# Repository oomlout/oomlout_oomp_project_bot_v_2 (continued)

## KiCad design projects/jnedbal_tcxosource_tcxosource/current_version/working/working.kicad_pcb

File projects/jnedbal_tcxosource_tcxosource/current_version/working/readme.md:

# tcxosource
 
## summary 
* id: jnedbal_tcxosource_tcxosource
* user: jnedbal
* name: tcxosource
* board: tcxosource
* repo: https://github.com/jnedbal/TCXOsource
* src_file_repo_kicad_pcb: TCXOsource.kicad_pcb
* src_file_repo_kicad_pcb_link: https://github.com/jnedbal/TCXOsource/tree/master/TCXOsource.kicad_pcb

* src_file_repo_sch: 
* src_file_repo_sch_link: https://github.com/jnedbal/TCXOsource/tree/master/
* full details link: https://github.com/oomlout/oomlout_oomp_project_bot_v_2/tree/main/projects/jnedbal_tcxosource_tcxosource/current_version/working

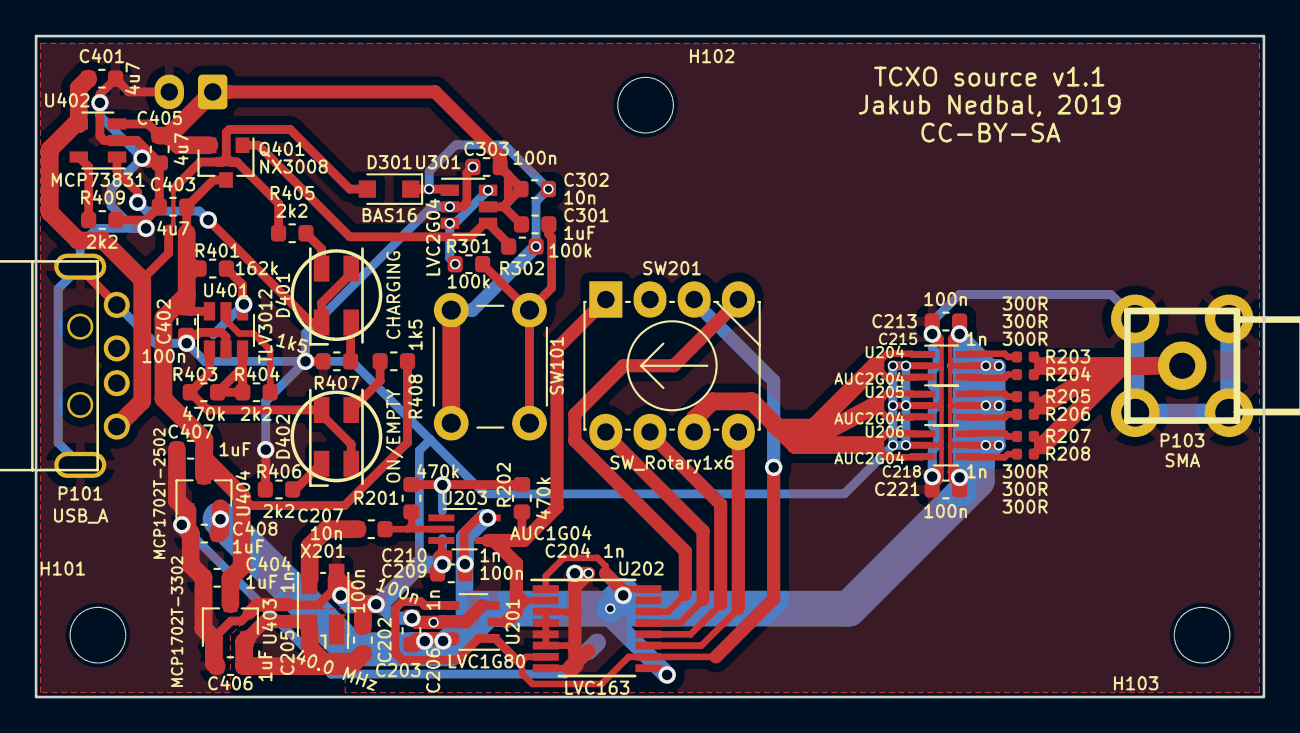
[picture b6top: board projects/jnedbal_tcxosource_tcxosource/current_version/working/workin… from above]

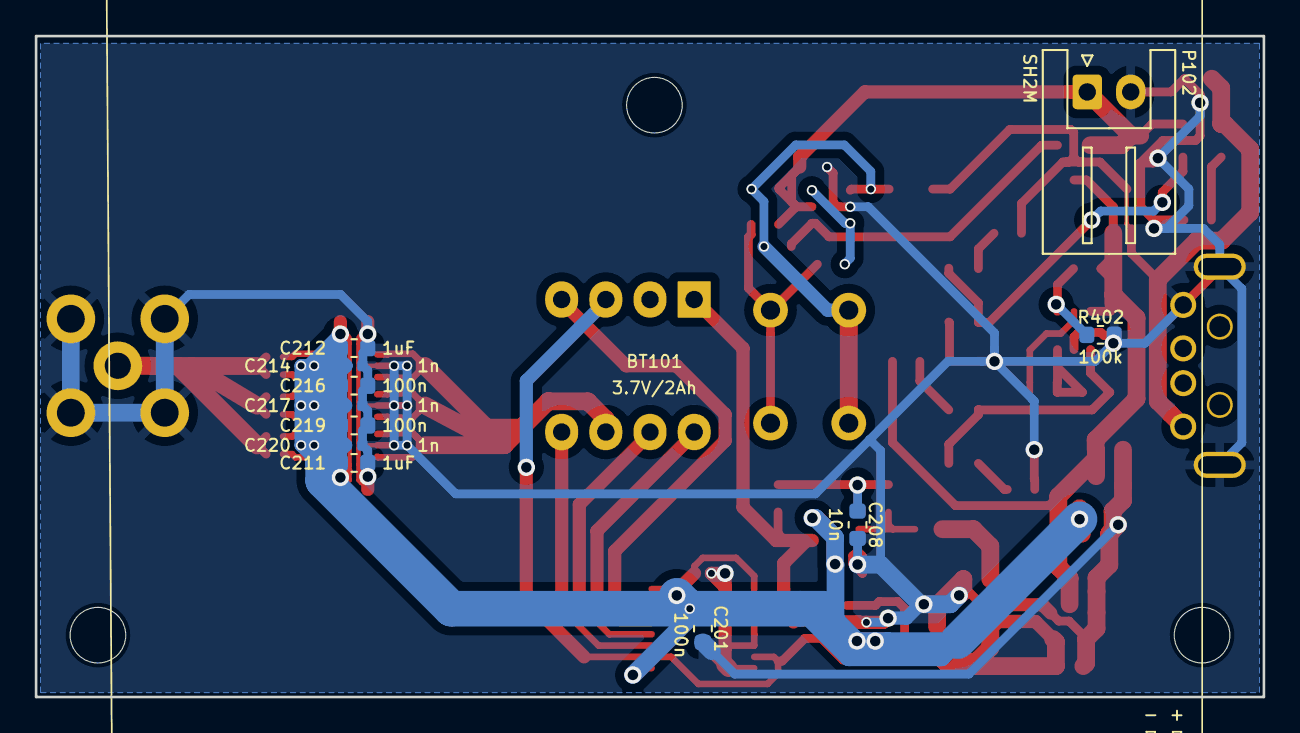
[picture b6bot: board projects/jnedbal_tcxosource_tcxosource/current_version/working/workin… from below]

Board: 2 copper layers, 70.6 x 38.0 mm, 76 parts (12 on the bottom side), 37 nets.

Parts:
BT101: 3.7V/2Ah; MIKROE-1120
C201, C202, C203, C209, C213, C216, C218, C219, C303, C402: 100n; C_0603_1608Metric
C204, C205, C206, C210, C214, C215, C217, C220, C221: 1n; C_0402_1005Metric
C207, C208, C302: 10n; C_0603_1608Metric
C211, C212, C301, C404, C406, C407, C408: 1uF; C_0603_1608Metric
C401, C403, C405: 4u7; C_0603_1608Metric
D301: BAS16; D_SOD-323_HandSoldering
D401, D402: LED_R/G; LEDdual_3.2x2.8
H101, H102, H103: MountingHole; MountingHole_3.2mm_M3
P101: USB_A; Molex_USB_A
P102: SH2M; JST_XH_S2B-XH-A_1x02_P2.50mm_Horizontal
P103: SMA
Q401: NX3008; SOT-23
R201, R202, R403: 470k; R_0603_1608Metric
R203, R204, R205, R206, R207, R208: 300R; R_0402_1005Metric
R301, R302, R402: 100k; R_0603_1608Metric
R401: 162k; R_0603_1608Metric
R404, R405, R406, R409: 2k2; R_0603_1608Metric
R407, R408: 1k5; R_0603_1608Metric
SW101: SW_Push; SW_PUSH_6mm_H13mm
SW201: SW_Rotary1x6; Nidec_Copal_SS-10-16
U201: LVC1G80; TSOP-5_1.65x3.05mm_P0.95mm
U202: LVC163; TSSOP-16_4.4x5mm_P0.65mm
U203: AUC1G04; SOT-353_SC-70-5_Handsoldering
U204, U205, U206: AUC2G04; SOT-363_SC-70-6_Handsoldering
U301: LVC2G04; SOT-23-6
U401: TLV3012; SOT-23-6
U402: MCP73831; SOT-23-5
U403: MCP1702T-3302; SOT-23
U404: MCP1702T-2502; SOT-23
X201: 40.0 MHz; Oscillator_SMD_EuroQuartz_XO32-4Pin_3.2x2.5mm_HandSoldering

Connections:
+2V5: C201.2, C203.2, C204.2, C206.2, C209.2, C210.1, C211.1, C212.1, C213.2, C214.1, C215.1, C216.2, C217.1, C218.2, C219.2, C220.1, C221.1, C408.1, U201.5, U202.1, U202.9, U202.16, U203.5, U204.5, U205.5, U206.5, U404.2
+3V3: C202.2, C205.2, C406.1, U403.2, X201.4
+3V8: C402.2, C403.1, C404.1, C407.1, Q401.3, R401.1, R408.1, U401.6, U403.3, U404.3
+5V: C401.1, D301.2, P101.1, R405.1, U402.4
+BATT: C301.1, C302.1, C303.2, C405.1, P102.1, Q401.2, U301.5, U402.3
/Charger & Power Supply/Bgrn: D402.2, R408.2
/Charger & Power Supply/Bred: D402.3, R406.1
/Charger & Power Supply/Cgrn: D401.4, R407.1
/Charger & Power Supply/Cred: D401.1, R405.2
/Charger & Power Supply/PROG: R409.1, U402.5
/Charger & Power Supply/REF: R404.2, U401.5
/Charger & Power Supply/STAT: D401.2, D401.3, U402.1
/Charger & Power Supply/TH: R403.1, R404.1, U401.3
/Charger & Power Supply/VSENSE: R401.2, R402.1, U401.4
/Charger & Power Supply/~V_OK: D402.1, D402.4, R403.2, U401.1
/SWITCH1: C301.2, R301.2, SW101.2
/SWITCH2: C302.2, D301.1, R302.2, SW101.1, U301.1
/TCXO/OUT: P103.1, R203.1, R204.1, R205.1, R206.1, R207.1, R208.1
/switch/POWER_ON: Q401.1, R302.1, U301.4
GND: C201.1, C202.1, C203.1, C204.1, C205.1, C206.1, C208.2, C209.1, C210.2, C211.2, C212.2, C213.1, C214.2, C215.2, C216.1, C217.2, C218.1, C219.1, C220.2, C221.2, C303.1, C401.2, C402.1, C403.2, C404.2, C405.2, C406.2, C407.2, C408.2, P101.4, P101.5, P102.2, P103.2, P103.3, P103.4, P103.5, R402.2, R406.2, R407.2, R409.2, U201.3, U202.3, U202.4, U202.5, U202.6, U202.8, U203.3, U204.2, U205.2, U206.2, U301.2, U401.2, U402.2, U403.1, U404.1, X201.2
unnamed: C207.1, R201.2, U203.2
unnamed: C207.2, X201.3
unnamed: C208.1, R201.1, R202.2
unnamed: R202.1, SW201.1, U201.2, U202.2, U203.4
unnamed: R203.2, U204.6
unnamed: R204.2, U204.4
unnamed: R205.2, U205.6
unnamed: R206.2, U205.4
unnamed: R207.2, U206.6
unnamed: R208.2, U206.4
unnamed: R301.1, U301.3, U301.6
unnamed: SW201.3, U201.1, U201.4, U202.7, U202.10
unnamed: SW201.4, U202.14
unnamed: SW201.5, U202.13
unnamed: SW201.6, U202.12
unnamed: SW201.7, U204.1, U204.3, U205.1, U205.3, U206.1, U206.3
unnamed: SW201.8, U202.11

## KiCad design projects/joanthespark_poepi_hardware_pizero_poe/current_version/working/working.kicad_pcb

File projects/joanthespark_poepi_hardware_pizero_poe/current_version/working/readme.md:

# poepi_hardware
 
## summary 
* id: joanthespark_poepi_hardware_pizero_poe
* user: joanthespark
* name: poepi_hardware
* board: pizero_poe
* repo: https://github.com/JoanTheSpark/PoEPi-hardware
* src_file_repo_kicad_pcb: ws2812-controller/pizero-poe.kicad_pcb
* src_file_repo_kicad_pcb_link: https://github.com/JoanTheSpark/PoEPi-hardware/tree/master/ws2812-controller/pizero-poe.kicad_pcb

* src_file_repo_sch: 
* src_file_repo_sch_link: https://github.com/JoanTheSpark/PoEPi-hardware/tree/master/
* full details link: https://github.com/oomlout/oomlout_oomp_project_bot_v_2/tree/main/projects/joanthespark_poepi_hardware_pizero_poe/current_version/working

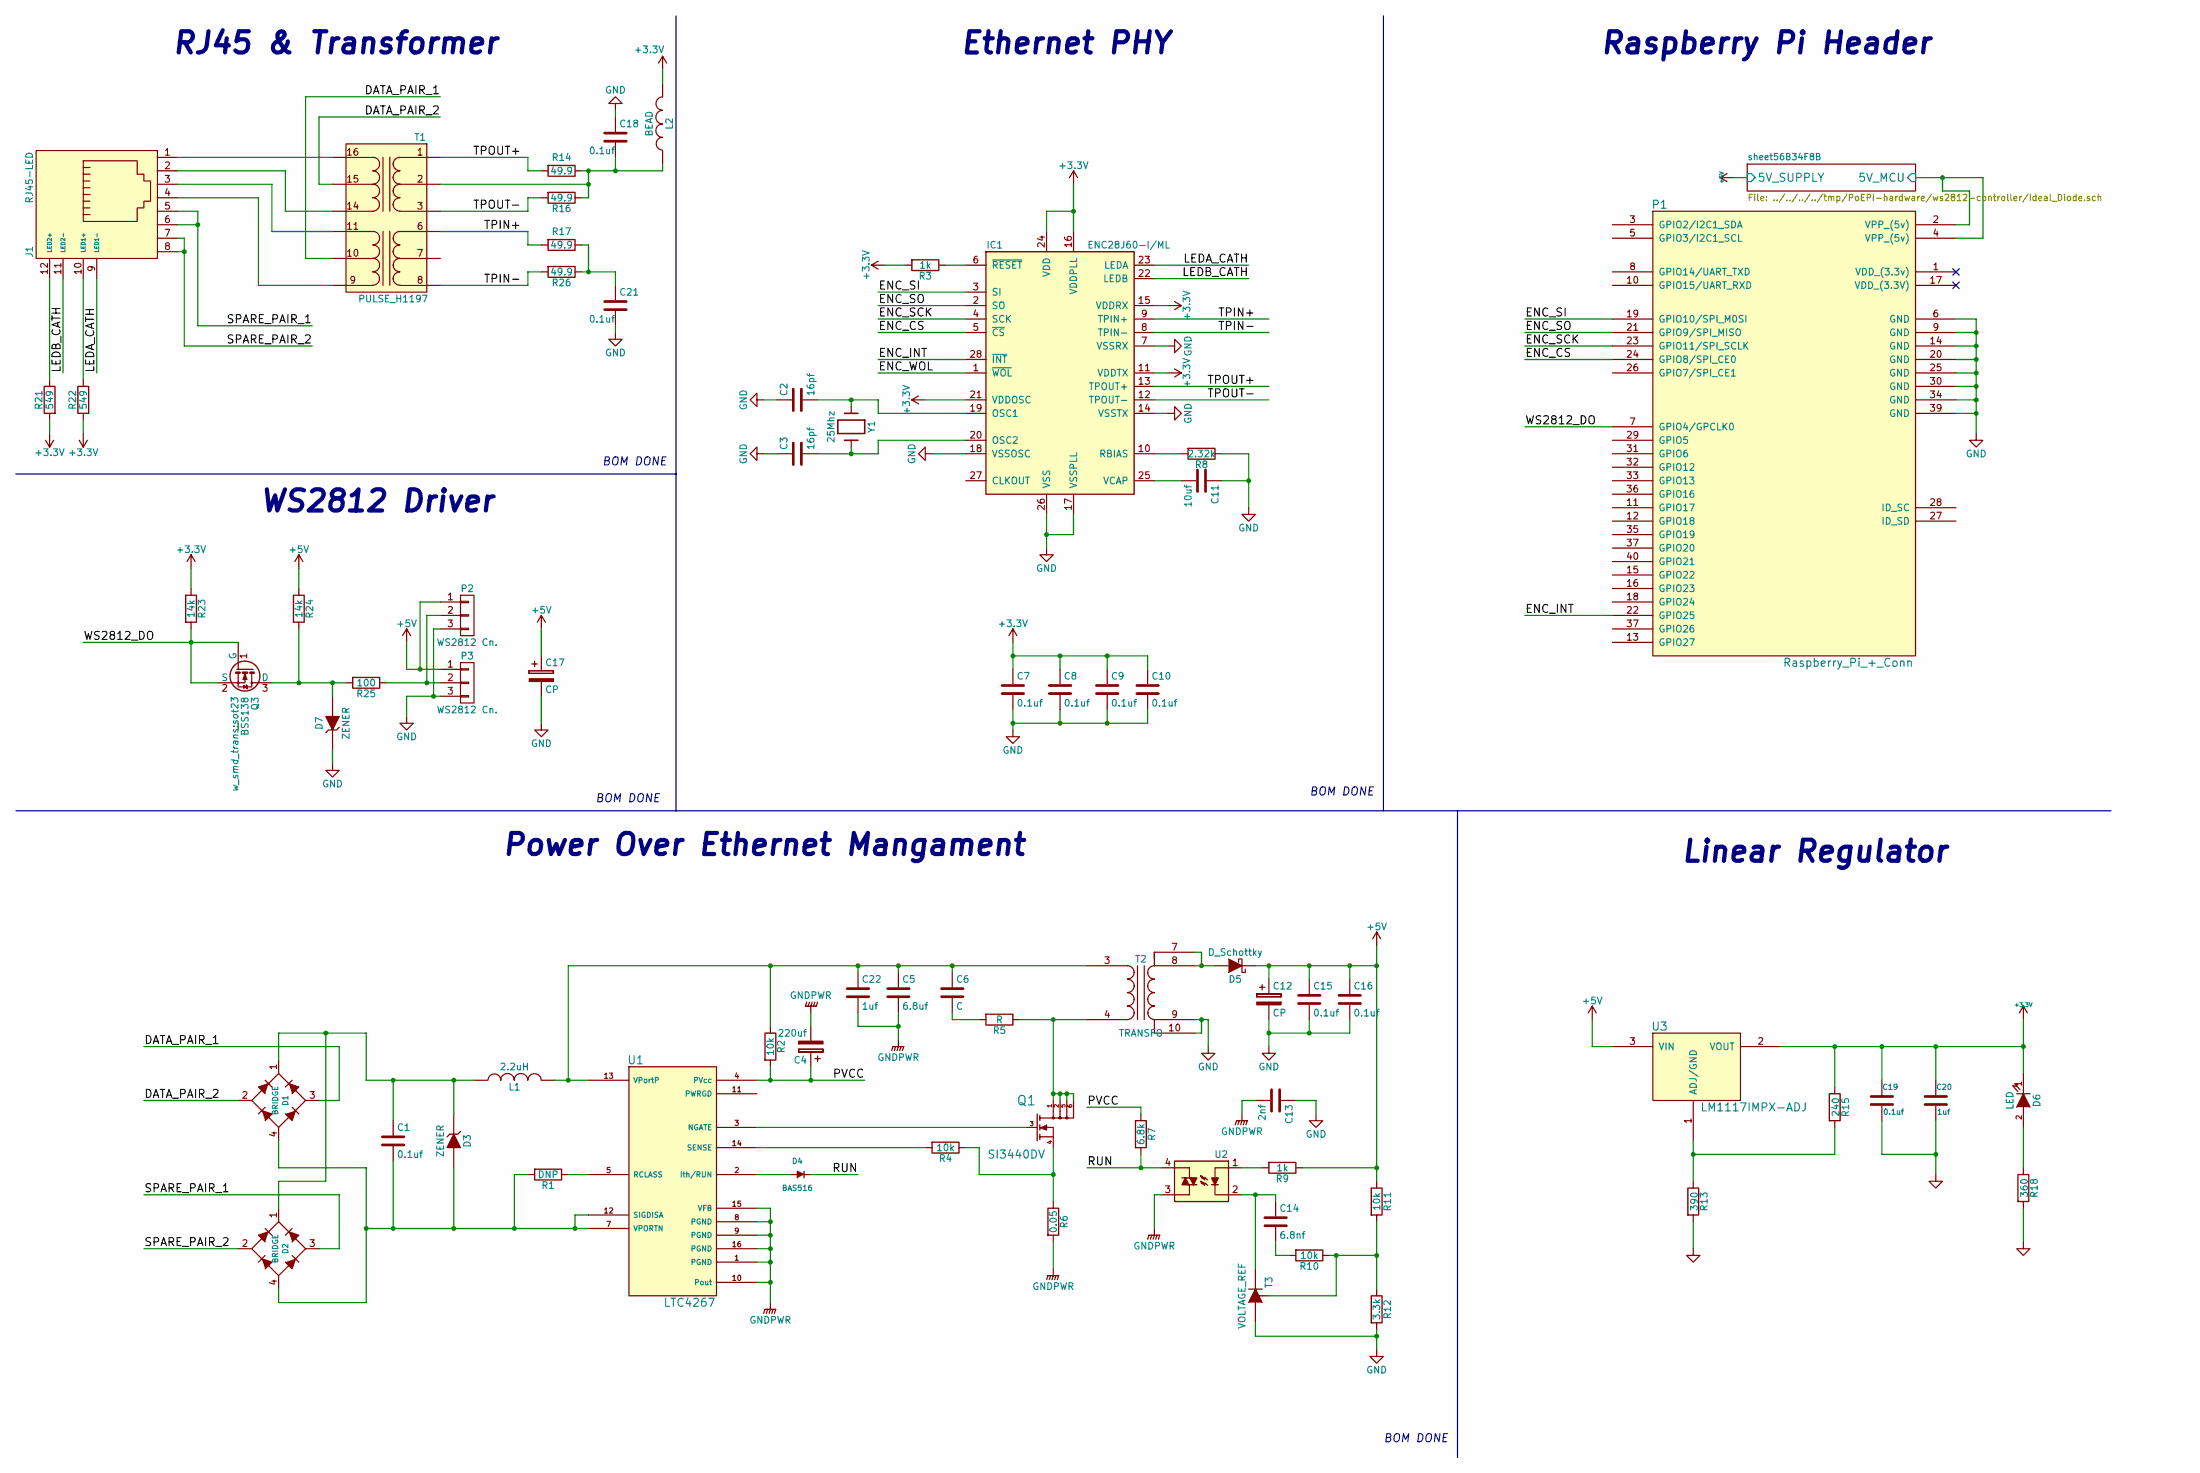
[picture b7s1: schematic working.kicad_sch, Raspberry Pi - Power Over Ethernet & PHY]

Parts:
C1, C7, C8, C9, C18, C19, C21: 0.1uf; c_0402; Mouser Part No. 710-885012105001
C2, C3: 16pf; c_0402; Mouser Part No. 81-GRM1555C1H160JA1D
C4: 220uf; c_tant_B; Mouser Part No. 581-TAJB475K025R
C5: 6.8uf; c_tant_D; Mouser Part No. 74-293D685X9050D2TE3
C6: C; c_0402
C10, C15, C16: 0.1uf; c_0603; Mouser Part No. 710-885012105001
C11: 10uf; c_0603; Mouser Part No. 81-ZRB18AR61C106ME1L
C12: CP; c_elec_4x4.5; Mouser Part No. 667-EEE-1AA330WR
C13: 2nf; c_0603; Mouser Part No. 81-GRM1885C1H202JA1D
C14: 6.8nf; c_0402; Mouser Part No. 81-GRM155R71H682KA8D
C17: CP; c_elec_8x6.5; Mouser Part No. 667-EEE-1AA221P
C20: 1uf; c_0402; Mouser Part No. 810-C1005X5R1H104K
C22: 1uf; c_0805; Mouser Part No. 810-C2012X7S2A105K
D1, D2: BRIDGE; MBS; Mouser Part No. 621-HD01-T
D3: ZENER; do214ac; Mouser Part No. 576-SMAJ58A
D4: BAS516; sod523; Mouser Part No. 771-BAS516-T/R
D5: D_Schottky; do214ab; Mouser Part No. 621-B360A-F
D6: LED; Led_0603; Mouser Part No. 743-HT-191USD
D7: ZENER; sod123; Mouser Part No. 771-BZT52HB5V1115
IC1: ENC28J60-I/ML; qfn-28; Mouser Part No. 579-ENC28J60-I/ML
J1: RJ45-LED; rj45-tyco-2-406549-7; Mouser Part No. 710-615008137421
L1: 2.2uH; inductor_smd_1008; Mouser Part No. 81-LQM2HPN2R2MEHL
L2: BEAD; inductor_smd_0402; Mouser Part No. 81-BLM15AG102SN1D
P1: Raspberry_Pi_+_Conn
P2: WS2812 Cn.; pin_strip_3
P3: WS2812 Cn.; pin_strip_3-90
Q1: SI3440DV; tsot-6; Mouser Part No. 781-SI3440DV-E3
Q3: BSS138; sot23; Mouser Part No. 512-BSS138
R1: DNP; r_0402
R2, R4, R10, R11: 10k; r_0402; Mouser Part No. 754-RR0510P-103D
R3: 1k; r_0402; Mouser Part No. 754-RR0510P-102D
R5: R; r_0402
R6: 0.05; r_1206; Mouser Part No. 660-UR732BTTD50L0F
R7: 6.8k; r_0402; Mouser Part No. 754-RR0510P-682D
R8: 2.32k; r_0402; Mouser Part No. 667-ERJ-2RKF2321X
R9: 1k; r_0402
R12: 3.3k; r_0402; Mouser Part No. 754-RR0510P-332D
R13: 390; r_0402; Mouser Part No. 594-MCT06030C3900FP5
R14, R16, R17, R26: 49.9; r_0402; Mouser Part No. 660-RK73H1ETQTP49R9F
R15: 240; r_0402; Mouser Part No. 754-RR0816P-241D
R18: 360; r_0402; Mouser Part No. 71-CRCW0603316RFKEB
R21, R22: 549; r_0402; Mouser Part No. 667-ERJ-2RKF5490X
R23, R24: 14k; r_0402; Mouser Part No. 667-ERJ-2RKF1402X
R25: 100; r_0402; Mouser Part No. 71-CRCW0402-100-E3
T1: PULSE_H1197; H2019; Mouser Part No. 673-H1197FNL
T2: TRANSFO; PoE_TRANS; Mouser Part No. 710-7491199501
T3: VOLTAGE_REF; sot23; Mouser Part No. 863-TLV431BSN1T1G
U1: LTC4267; ssop-16; Digikey Part No. LTC4267CGN-3#PBF-ND
U2: PAS291; OPTO_ISO; Mouser Part No. 551-PS2911-1-K-AX
U3: LM1117IMPX-ADJ; sot223; Mouser Part No. 926-M1117IMPXADJNOPB
Y1: 25Mhz; crystal_smd_5x3.2mm; Mouser Part No. 774-445I23D25M00000

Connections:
+3V3: C7.1, C8.1, C9.1, C10.1, C19.1, C20.1, D6.1 (K), IC1.11 (VDDTX), IC1.15 (VDDRX), IC1.16 (VDDPLL), IC1.21 (VDDOSC), IC1.24 (VDD), L2.2, R3.2, R15.1, R21.2, R22.2, R23.1, U3.2 (VOUT)
+5V: C12.1, C15.1, C16.1, C17.1, D5.1 (K), P2.1, P3.1, R9.1, R11.1, R24.1, U3.3 (VIN); also elsewhere on the board
/DATA_PAIR_1: D1.3 (~2), T1.10
/DATA_PAIR_2: D1.2 (~1), T1.15
/ENC_CS: IC1.5 (~CS), P1.24 (GPIO8/SPI_CE0)
/ENC_INT: IC1.28 (~INT), P1.22 (GPIO25)
/ENC_SCK: IC1.4 (SCK), P1.23 (GPIO11/SPI_SCLK)
/ENC_SI: IC1.3 (SI), P1.19 (GPIO10/SPI_M0SI)
/ENC_SO: IC1.2 (SO), P1.21 (GPIO9/SPI_MISO)
/ENC_WOL: IC1.1 (~WOL)
/LEDA_CATH: IC1.23 (LEDA), J1.9 (LED1-)
/LEDB_CATH: IC1.22 (LEDB), J1.11 (LED2-)
/PVCC: C4.1, R2.2, R7.1, U1.4 (PVcc)
/RUN: D4.2 (K), R7.2, U2.4
/SPARE_PAIR_1: D2.3 (~2), J1.5, J1.6
/SPARE_PAIR_2: D2.2 (~1), J1.7, J1.8
/TPIN+: IC1.9 (TPIN+), R17.2, T1.6 (PR1)
/TPIN-: IC1.8 (TPIN-), R26.2, T1.8 (PR2)
/TPOUT+: IC1.13 (TPOUT+), R14.2, T1.1 (PR1)
/TPOUT-: IC1.12 (TPOUT-), R16.2, T1.3 (PR2)
/WS2812_DO: P1.7 (GPIO4/GPCLK0), Q3.1 (G), Q3.2 (S), R23.2
/sheet56B34F8B/5V_MCU: P1.2 (VPP_(5v)), P1.4 (VPP_(5v)); also elsewhere on the board
GND: C2.1, C3.1, C7.2, C8.2, C9.2, C10.2, C11.1, C12.2, C13.1, C15.2, C16.2, C17.2, C18.1, C19.2, C20.2, C21.2, D7.1 (K), IC1.7 (VSSRX), IC1.14 (VSSTX), IC1.17 (VSSPLL), IC1.18 (VSSOSC), IC1.26 (VSS), P1.6 (GND), P1.9 (GND), P1.14 (GND), P1.20 (GND), P1.25 (GND), P1.30 (GND), P1.34 (GND), P1.39 (GND), P2.3, P3.3, R8.1, R12.2, R13.2, R18.2, T2.9 (SA), T2.10, T3.2 (A); also elsewhere on the board
GNDPWR: C4.2, C5.2, C13.2, C22.2, R6.2, U1.1 (PGND), U1.8 (PGND), U1.9 (PGND), U1.10 (Pout), U1.15 (VFB), U1.16 (PGND), U2.3
unnamed: C1.1, D1.1 (V+), D2.1 (V+), D3.1 (K), L1.1
unnamed: C1.2, D1.4 (V-), D2.4 (V-), D3.2 (A), R1.2, U1.7 (VPORTN), U1.12 (SIGDISA)
unnamed: C2.2, IC1.19 (OSC1), Y1.1
unnamed: C3.2, IC1.20 (OSC2), Y1.2
unnamed: C6.2, R5.2
unnamed: C11.2, IC1.25 (VCAP)
unnamed: C14.1, T3.3 (K), U2.2
unnamed: C14.2, R10.2
unnamed: C18.2, L2.1, R14.1, R16.1, T1.2 (PM)
unnamed: C21.1, R17.1, R26.1
unnamed: C5.1, C6.1, C22.1, L1.2, R2.1, T2.3 (AA), U1.13 (VPortP)
unnamed: D4.1 (A), U1.2 (Ith/RUN)
unnamed: D5.2 (A), T2.7, T2.8 (SB)
unnamed: D6.2 (A), R18.1
unnamed: D7.2 (A), Q3.3 (D), R24.2, R25.2
unnamed: IC1.6 (~RESET), R3.1
unnamed: IC1.10 (RBIAS), R8.2
unnamed: J1.1, T1.16 (S2)
unnamed: J1.2, T1.14 (S1)
unnamed: J1.3, T1.11 (S2)
unnamed: J1.4, T1.9 (S1)
unnamed: J1.10 (LED1+), R22.1
unnamed: J1.12 (LED2+), R21.1
unnamed: P2.2, P3.2, R25.1
unnamed: Q1.1 (D), Q1.2 (D), Q1.5 (D), Q1.6 (D), R5.1, T2.4 (AB)
unnamed: Q1.3 (G), U1.3 (NGATE)
unnamed: Q1.4 (S), R4.1, R6.1
unnamed: R1.1, U1.5 (RCLASS)
unnamed: R4.2, U1.14 (SENSE)
unnamed: R9.2, U2.1
unnamed: R10.1, R11.2, R12.1, T3.1 (G)
unnamed: R13.1, R15.2, U3.1 (ADJ/GND)

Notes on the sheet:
BOM DONE
Ethernet PHY
Raspberry Pi Header
WS2812 Driver
Linear Regulator
Power Over Ethernet Mangament
RJ45 & Transformer

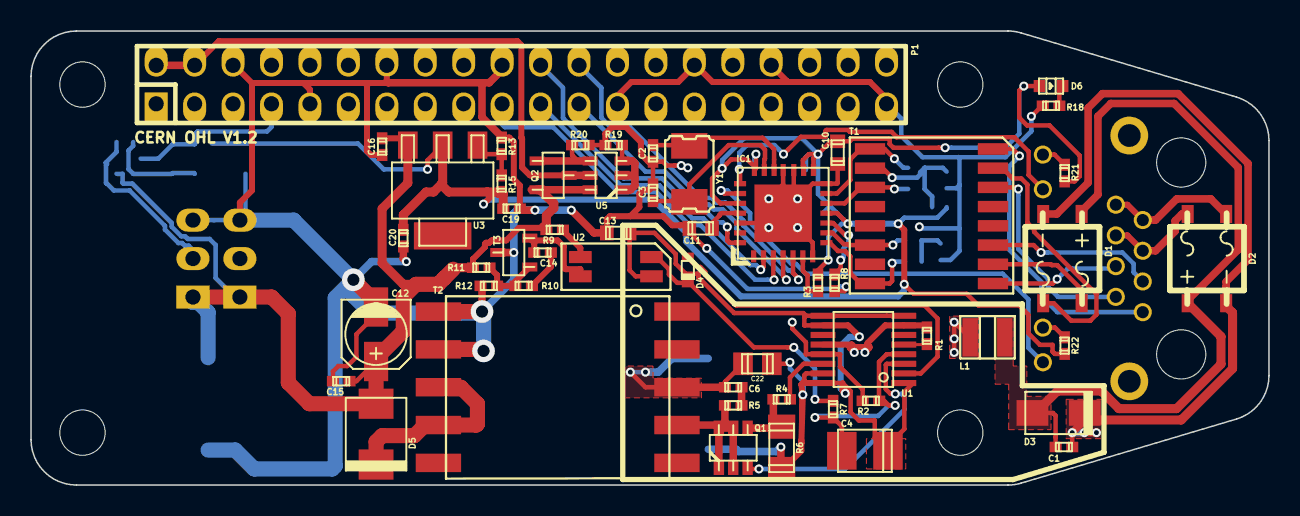
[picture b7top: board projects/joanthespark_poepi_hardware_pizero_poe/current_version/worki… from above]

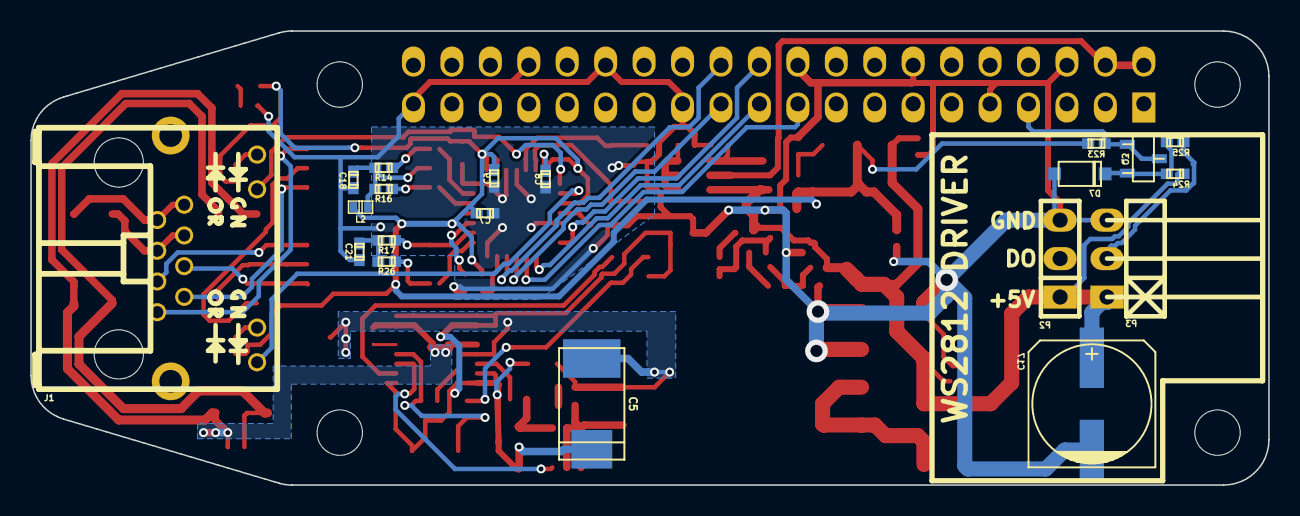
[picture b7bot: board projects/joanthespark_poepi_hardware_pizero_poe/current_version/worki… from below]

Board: 2 copper layers, 81.8 x 30.0 mm, 77 parts (20 on the bottom side), 57 nets.

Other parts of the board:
MT1, MT2, MT3, MT4: MountingHole_3mm
Q2: BSS138; sot23
R19: 10k; r_0402
R20: 47k; r_0402
U5: DMMT5401; sot23-6

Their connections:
+5V: Q2.3, U5.6; also elsewhere on the board
/sheet56B34F8B/5V_MCU: Q2.2, U5.5; also elsewhere on the board
GND: R19.2, R20.2; also elsewhere on the board
unnamed: Q2.1, R20.1, U5.4
unnamed: R19.1, U5.1, U5.2, U5.3
